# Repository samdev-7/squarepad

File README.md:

# Square Pad

A small but versatile macropad!

Square pad is a KMK-powered, 8-key macropad with a rotary encoder, OLED display, and underglow lighting.  
It's inspired by the [Ocreeb MK2](https://github.com/sb-ocr/ocreeb-mk-2/tree/main) and was built for the [Hackpad](https://hackpad.hackclub.com/) program.

### Profile switching

The Square Pad can store and switch between several profiles, adapting the 8 keys and rotary encoder to whatever you need.  
To switch between presets, click the rotary encoder, rotate it to select a profile (shown on the OLED screen), and click to confirm. The underglow lighting will change colors, letting you know the current profile at a glance.

# Design

This is my first time designing a macropad/keyboard! Tons of Googling and bugging others here and there, but I (hopefully) did it!

## PCB

A total of 0 vias are on the PCB, ignoring THT and mounting holes. (there's no benefit to this, don't ask why)

The PCB was designed in KiCad

## Case

The entire case can be 3D printed in 3 parts and assembled only with 6 M2x16mm screws and a tiny bit of hot glue for the screen. Each part is optimized for printability and quality with almost no supports.

The case was designed in Onshape

## Firmware

Square Pad is powered by custom firmware written with [KMK](https://github.com/KMKfw/kmk_firmware). The custom firmware enabled easy profile switching and configuration.

# BOM

Everything you need to make your own Square Pad, minus the solder, glue, sweat, and tears.

## Electronics

- 1x XIAO RP2040 (with headers)
- 1x EC11E Rotary Encoder (with switch)
- 1x Rotary Encoder Knob
- 1x 0.91" OLED Display
- 8x Cherry MX Switches
- 8x Blank DSA Keycaps
- 9x Diode (THT)
- 12x SK6812 Mini LEDs
- Wires (for display)

## Case

- 6x M2x16mm Screw
- 1x case_top.stl
- 1x case_mid.stl
- 1x case_btm.stl
- 4x 10mm Rubber Feet (or just use hot glue)

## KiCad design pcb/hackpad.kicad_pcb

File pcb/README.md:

# PCB

This folder contains the PCB for the Squre Pad, designed in KiCad 8.0

To manufacture your own Square Pad PCB, the gerbers for JLCPCB are in `/production`.

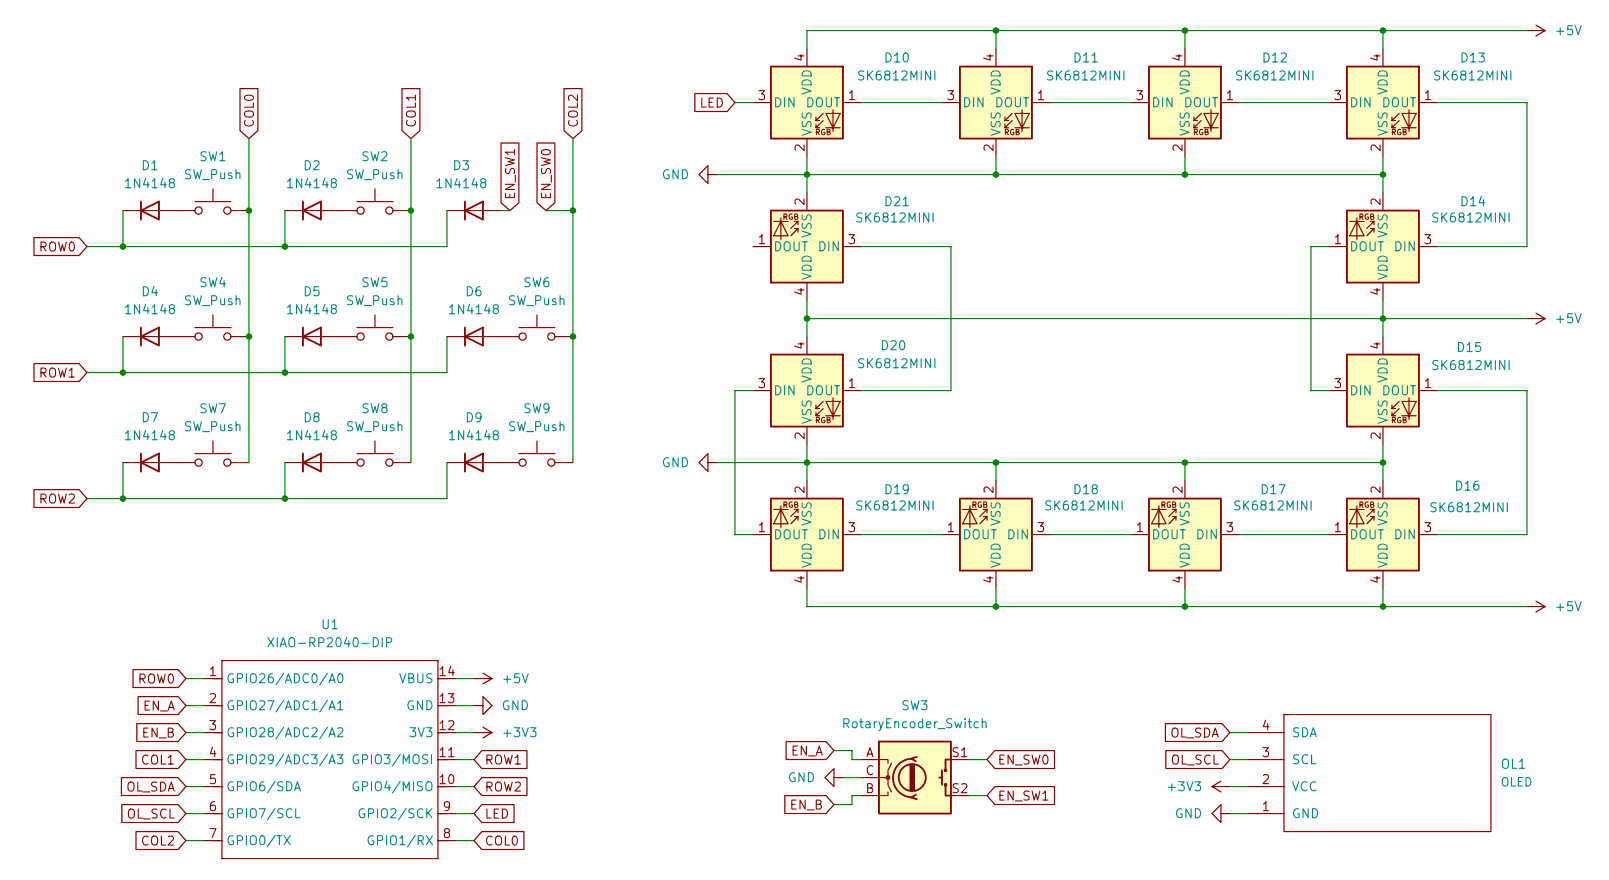
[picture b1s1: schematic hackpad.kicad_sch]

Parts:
D1, D2, D3, D4, D5, D6, D7, D8, D9: 1N4148; D_DO-35_SOD27_P7.62mm_Horizontal
D10, D11, D12, D13, D14, D15, D16, D17, D18, D19, D20, D21: SK6812MINI; LED_SK6812MINI_PLCC4_3.5x3.5mm_P1.75mm
OL1: OLED; SSD1306-0.91-OLED-4pin-128x32
SW1, SW2, SW4, SW5, SW6, SW7, SW8, SW9: SW_Push; SW_Cherry_MX_1.00u_PCB
SW3: RotaryEncoder_Switch; RotaryEncoder_Alps_EC11E-Switch_Vertical_H20mm
U1: XIAO-RP2040-DIP

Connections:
+3V3: OL1.2 (VCC), U1.12 (3V3)
+5V: D10.4 (VDD), D11.4 (VDD), D12.4 (VDD), D13.4 (VDD), D14.4 (VDD), D15.4 (VDD), D16.4 (VDD), D17.4 (VDD), D18.4 (VDD), D19.4 (VDD), D20.4 (VDD), D21.4 (VDD), U1.14 (VBUS)
COL0: SW1.2, SW4.2, SW7.2, U1.8 (GPIO1/RX)
COL1: SW2.2, SW5.2, SW8.2, U1.4 (GPIO29/ADC3/A3)
COL2: SW3.S1, SW6.2, SW9.2, U1.7 (GPIO0/TX)
EN_A: SW3.A, U1.2 (GPIO27/ADC1/A1)
EN_B: SW3.B, U1.3 (GPIO28/ADC2/A2)
EN_SW1: D3.2 (A), SW3.S2
GND: D10.2 (VSS), D11.2 (VSS), D12.2 (VSS), D13.2 (VSS), D14.2 (VSS), D15.2 (VSS), D16.2 (VSS), D17.2 (VSS), D18.2 (VSS), D19.2 (VSS), D20.2 (VSS), D21.2 (VSS), OL1.1 (GND), SW3.C, U1.13 (GND)
LED: D10.3 (DIN), U1.9 (GPIO2/SCK)
unnamed: D1.2 (A), SW1.1
unnamed: D2.2 (A), SW2.1
unnamed: D4.2 (A), SW4.1
unnamed: D5.2 (A), SW5.1
unnamed: D6.2 (A), SW6.1
unnamed: D7.2 (A), SW7.1
unnamed: D8.2 (A), SW8.1
unnamed: D9.2 (A), SW9.1
unnamed: D10.1 (DOUT), D11.3 (DIN)
unnamed: D11.1 (DOUT), D12.3 (DIN)
unnamed: D12.1 (DOUT), D13.3 (DIN)
unnamed: D13.1 (DOUT), D14.3 (DIN)
unnamed: D14.1 (DOUT), D15.3 (DIN)
unnamed: D15.1 (DOUT), D16.3 (DIN)
unnamed: D16.1 (DOUT), D17.3 (DIN)
unnamed: D17.1 (DOUT), D18.3 (DIN)
unnamed: D18.1 (DOUT), D19.3 (DIN)
unnamed: D19.1 (DOUT), D20.3 (DIN)
unnamed: D20.1 (DOUT), D21.3 (DIN)
OL_SCL: OL1.3 (SCL), U1.6 (GPIO7/SCL)
OL_SDA: OL1.4 (SDA), U1.5 (GPIO6/SDA)
ROW0: D1.1 (K), D2.1 (K), D3.1 (K), U1.1 (GPIO26/ADC0/A0)
ROW1: D4.1 (K), D5.1 (K), D6.1 (K), U1.11 (GPIO3/MOSI)
ROW2: D7.1 (K), D8.1 (K), D9.1 (K), U1.10 (GPIO4/MISO)

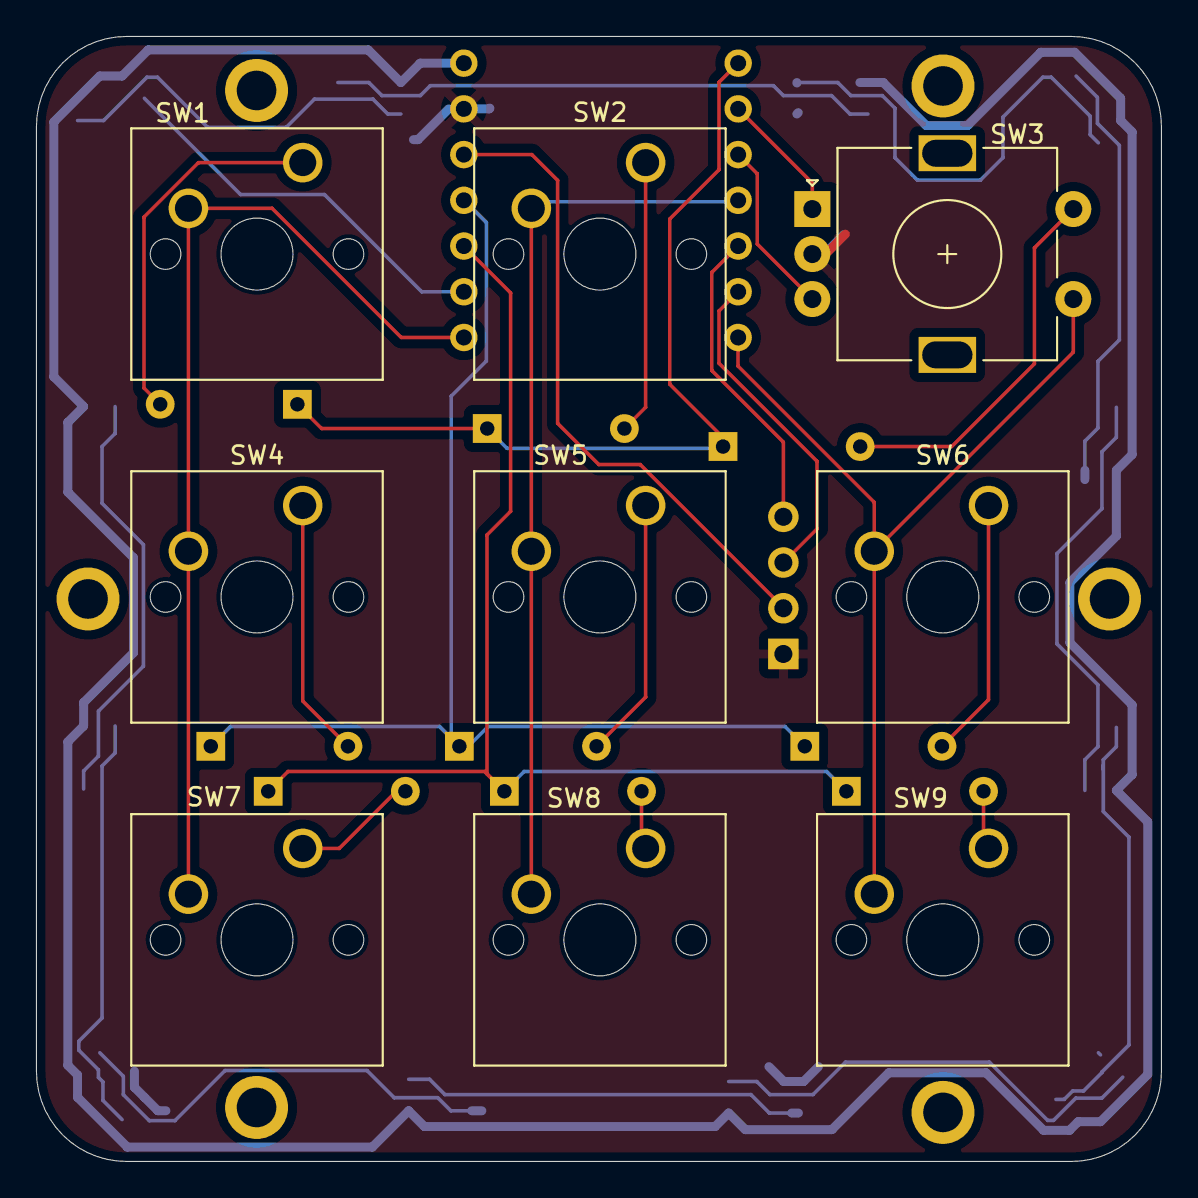
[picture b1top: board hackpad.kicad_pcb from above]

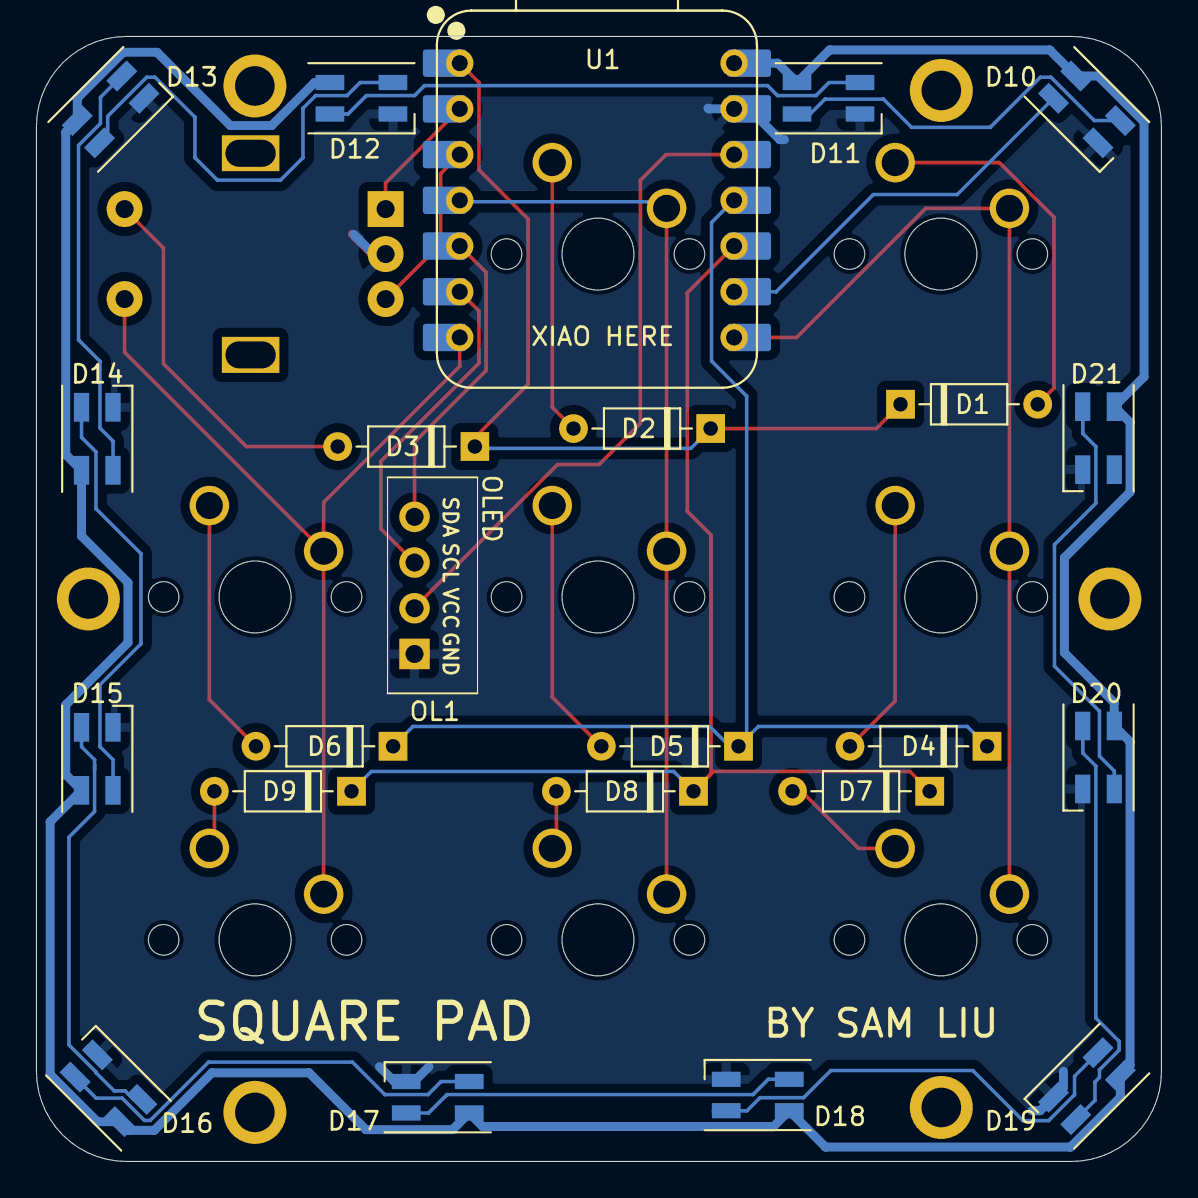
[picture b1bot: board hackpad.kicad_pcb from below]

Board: 2 copper layers, 62.5 x 62.5 mm, 32 parts (23 on the bottom side), 34 nets.

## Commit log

2025-06-07 Create LICENSE
2025-06-07 Create temp
2025-06-07 Upload PCB
2025-06-07 Add production files
2025-06-11 Add firmware
2025-06-11 Fix keymap
2025-06-11 Fix typo
2025-06-14 Fix OLED voltage
2025-07-27 Update hackpad
2025-07-27 Upate Hackpad
2025-08-12 Firmware update!
